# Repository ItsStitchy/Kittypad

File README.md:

# 🐾 Kittypad

Kittypad is a custom 4-key macropad featuring an EC11 rotary encoder and an integrated OLED display subsystem built using the Seeed Studio XIAO form factor. 

The ultimate goal for this hardware ecosystem is to run an interactive, embedded virtual pet (Tamagotchi-style) utilizing pixel art frame buffers mapped directly over I2C communication lines.

## 🛠️ Hardware Features
* **Microcontroller:** Seeed Studio XIAO
* **Keys:** 4 mechanical switches (Direct-pin layout to Ground)
* **Rotary Encoder:** 1 EC11 volume scroller with a press-to-mute button mapping.
* **Display Interface:** SSD1306 I2C OLED display ready for custom pixel rendering.
* **RGB Flare:** 1 onboard/underglow WS2812B NeoPixel.

Attached below is the schematic

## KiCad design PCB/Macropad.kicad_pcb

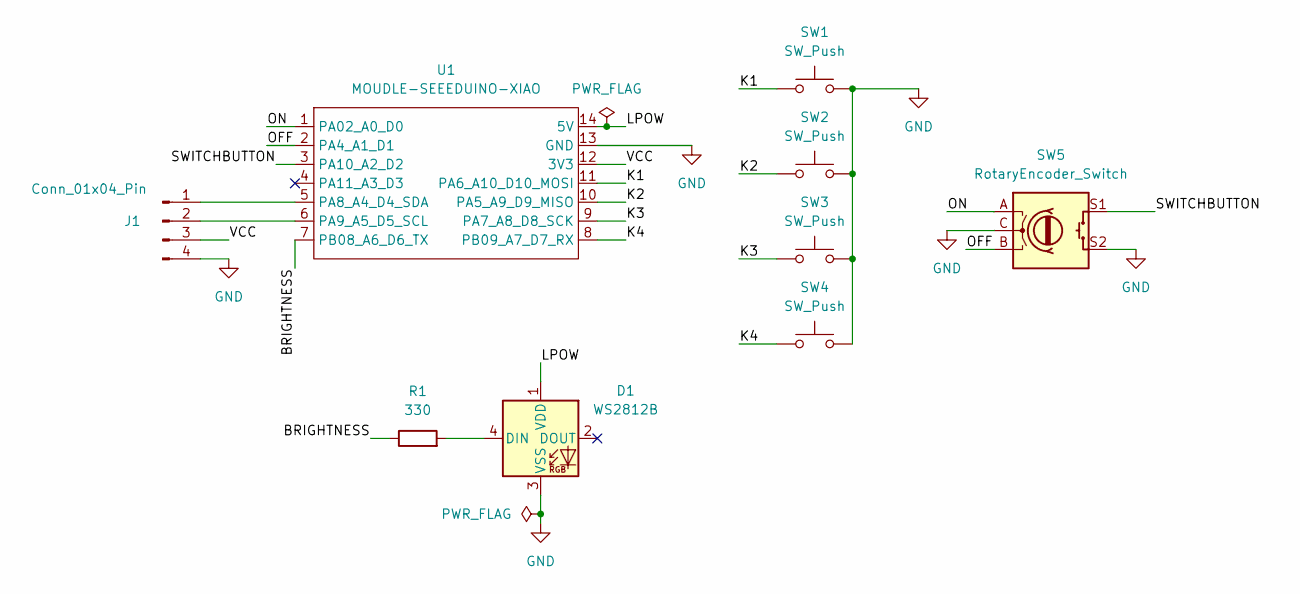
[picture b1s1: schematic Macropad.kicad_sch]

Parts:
D1: WS2812B; LED_WS2812B_PLCC4_5.0x5.0mm_P3.2mm
J1: Conn_01x04_Pin; PinHeader_1x04_P2.54mm_Vertical
R1: 330; R_0805_2012Metric
SW1, SW2, SW3, SW4: SW_Push; SW_Cherry_MX_1.00u_PCB
SW5: RotaryEncoder_Switch; RotaryEncoder_Alps_EC11E-Switch_Vertical_H20mm
U1: MOUDLE-SEEEDUINO-XIAO; XIAO-Generic-Hybrid-14P-2.54-21X17.8MM

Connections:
/BRIGHTNESS: R1.1, U1.7 (PB08_A6_D6_TX)
/K1: SW1.1, U1.11 (PA6_A10_D10_MOSI)
/K2: SW2.1, U1.10 (PA5_A9_D9_MISO)
/K3: SW3.1, U1.9 (PA7_A8_D8_SCK)
/K4: SW4.1, U1.8 (PB09_A7_D7_RX)
/LPOW: D1.1 (VDD), U1.14 (5V)
/OFF: SW5.B, U1.2 (PA4_A1_D1)
/ON: SW5.A, U1.1 (PA02_A0_D0)
/SWITCHBUTTON: SW5.S1, U1.3 (PA10_A2_D2)
/VCC: J1.3, U1.12 (3V3)
GND: D1.3 (VSS), J1.4, SW1.2, SW2.2, SW3.2, SW4.2, SW5.C, SW5.S2, U1.13 (GND)
unnamed: D1.4 (DIN), R1.2
unnamed: J1.1, U1.5 (PA8_A4_D4_SDA)
unnamed: J1.2, U1.6 (PA9_A5_D5_SCL)

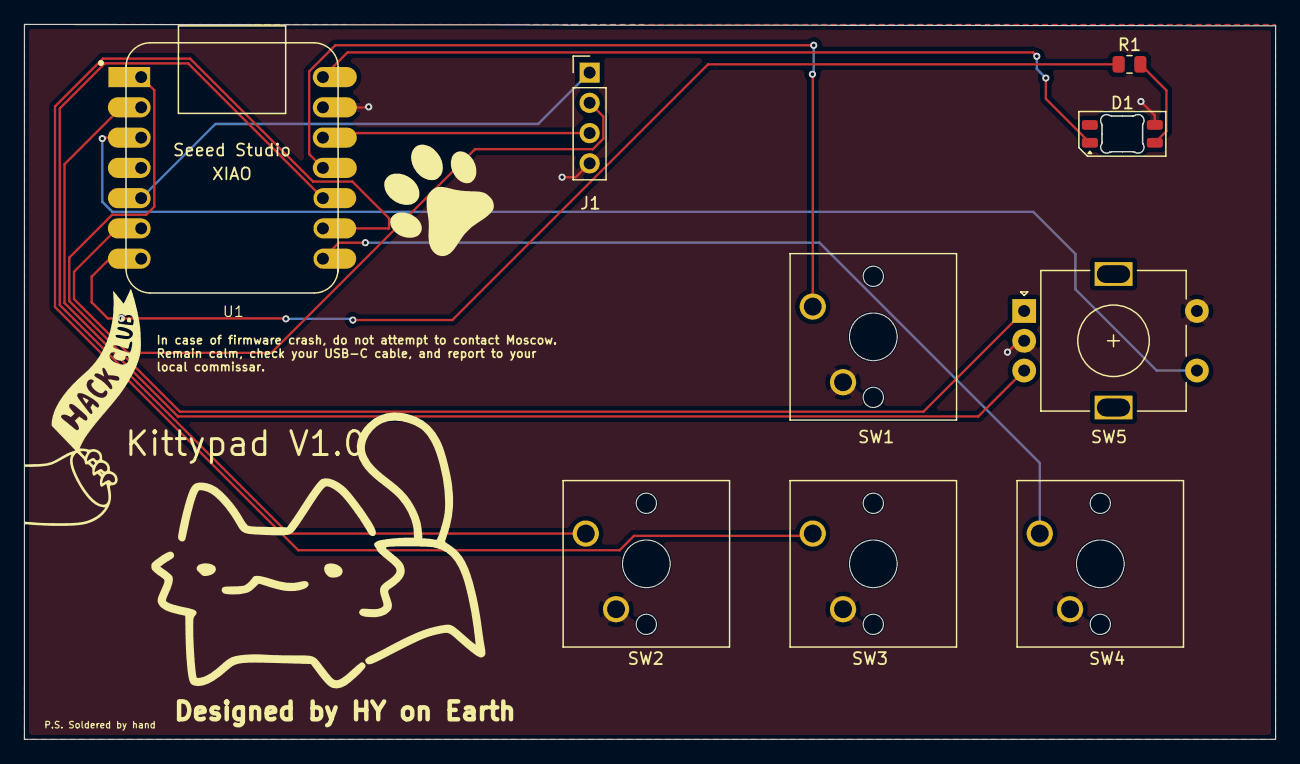
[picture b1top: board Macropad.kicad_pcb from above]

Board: 2 copper layers, 105.0 x 60.0 mm, 9 parts (0 on the bottom side), 14 nets.

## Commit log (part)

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2026-06-02 Create LICENSE
2026-06-28 Add info.json for Kittypad keyboard configuration
2026-06-28 Add build configuration for RP2040 firmware
2026-06-28 Add keymap and encoder functionality for firmware
2026-06-28 Enhance README with Kittypad project details
    Added detailed description and hardware features for Kittypad project.
2026-06-28 Add BOM.csv with component details and prices
